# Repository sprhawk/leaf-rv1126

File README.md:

# Leaf RV1126

This work is licensed under a [Creative Commons Attribution-ShareAlike 4.0 International License](http://creativecommons.org/licenses/by-sa/4.0/).

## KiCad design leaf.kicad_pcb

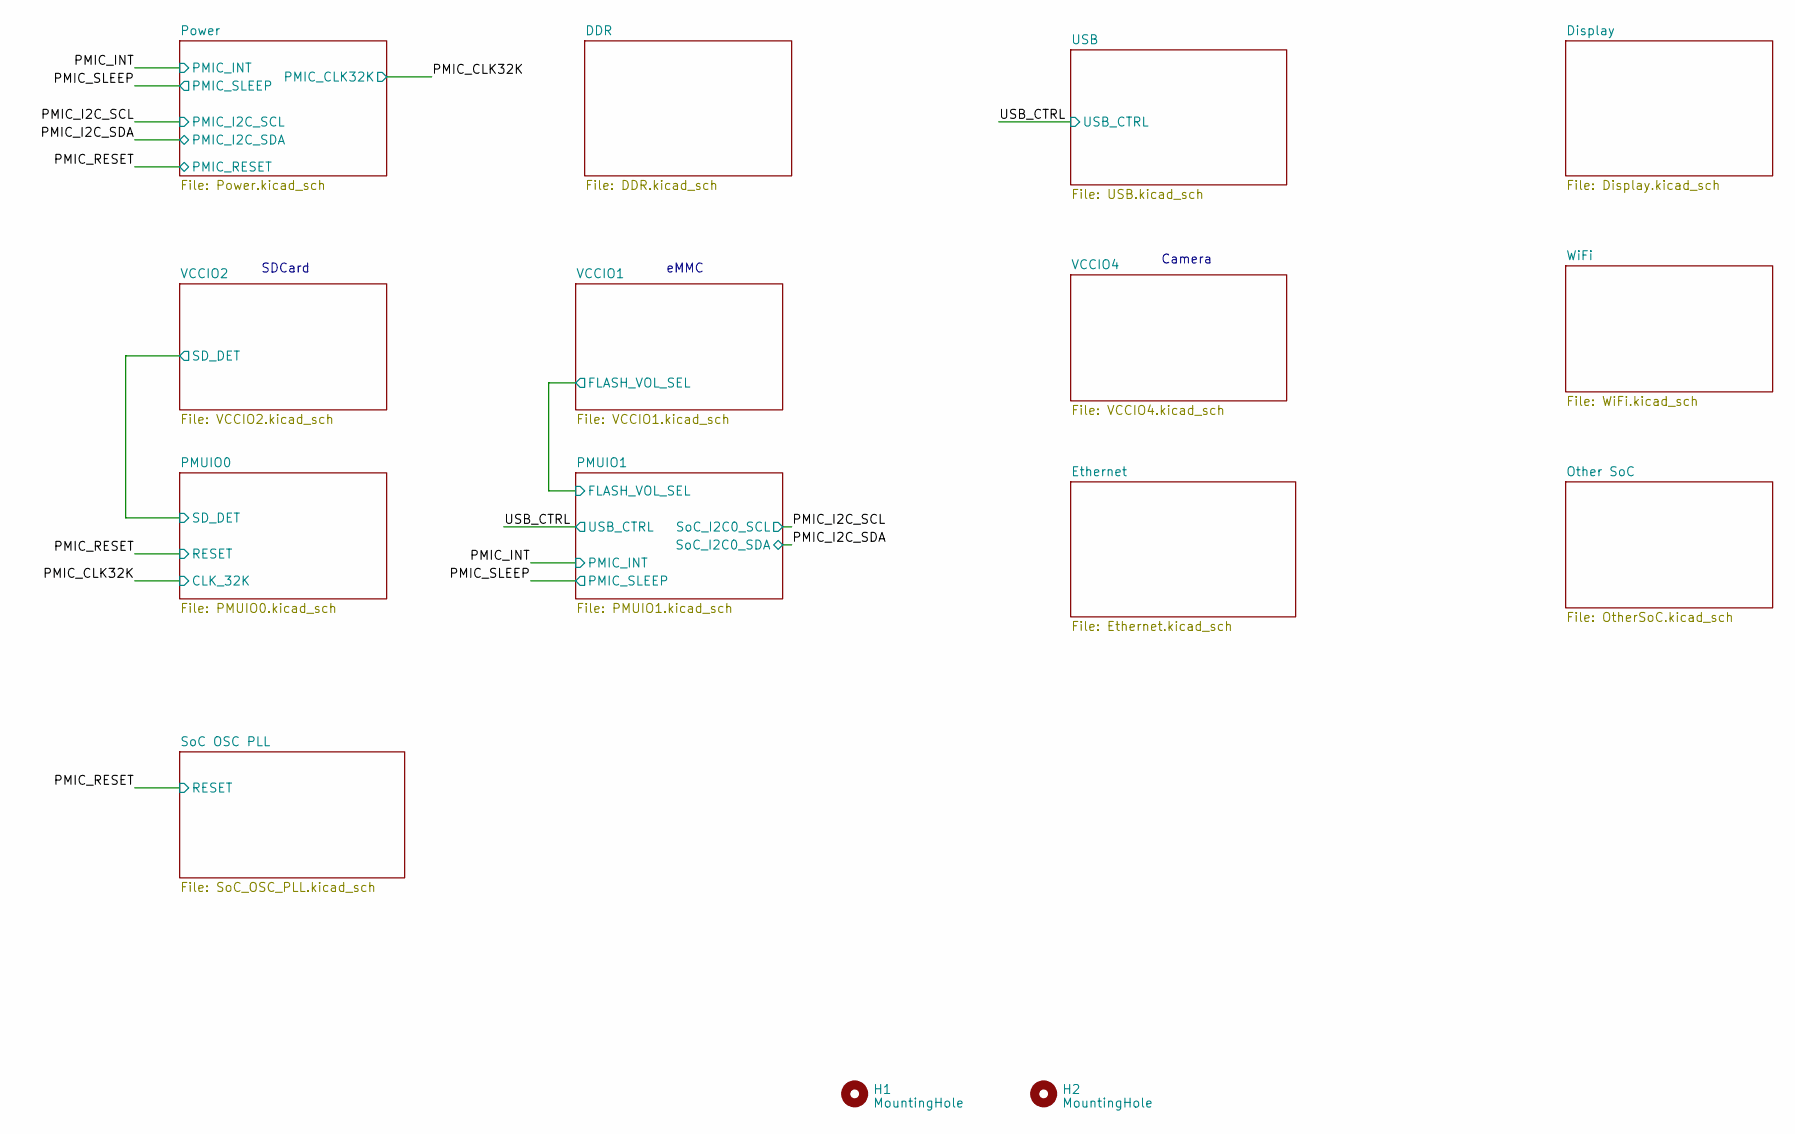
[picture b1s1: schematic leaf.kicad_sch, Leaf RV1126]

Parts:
H1, H2: MountingHole; MountingHole_2.7mm_M2.5

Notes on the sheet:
Camera
SDCard
eMMC

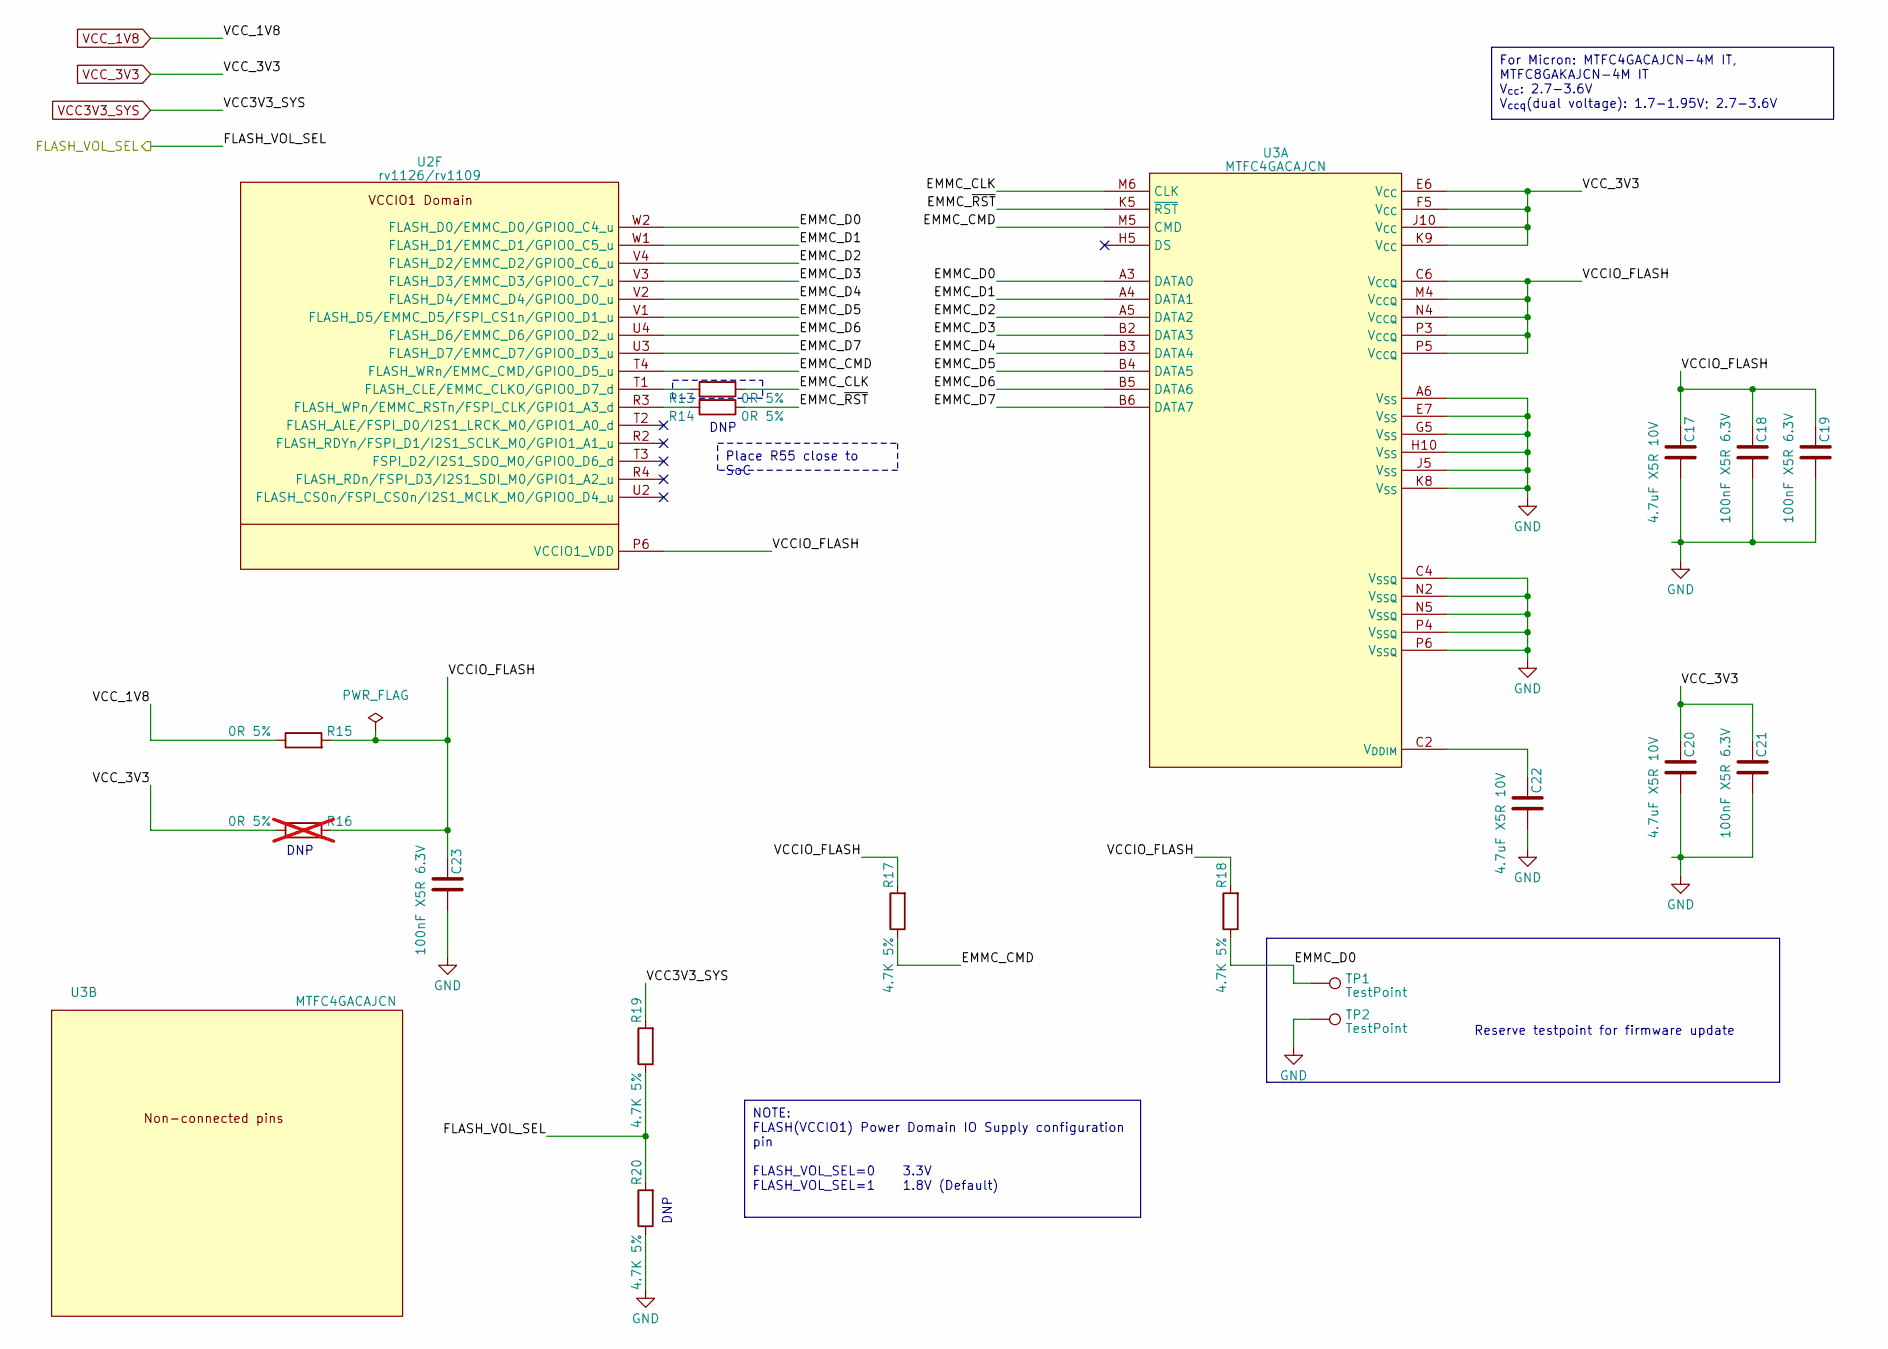
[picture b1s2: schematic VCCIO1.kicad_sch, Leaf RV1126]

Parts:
C17, C20, C22: 4.7uF X5R 10V; C_0402_1005Metric; LCSC C77004
C18, C19, C21, C23: 100nF X5R 6.3V; C_0201_0603Metric; LCSC C76928
R13, R14, R15: 0R 5%; R_0402_1005Metric; LCSC C17168
R16: 0R 5%; R_0402_1005Metric; LCSC C17168; not fitted
R17, R18, R19, R20: 4.7K 5%; R_0402_1005Metric; LCSC C25940
TP1, TP2: TestPoint; TestPoint_Pad_D1.0mm
U2: rv1126/rv1109; Rockchip_RV1126_FCCSP409LD_14.0x14.0mm
U3: MTFC4GACAJCN; Micron_eMMC_FBGA-153_11.5x13.0mm

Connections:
/PMUIO1/FLASH_VOL_SEL: R19.1, R20.2; also elsewhere on the board
/VCCIO1/EMMC_CLK: R13.1, U3.M6 (CLK)
/VCCIO1/EMMC_CMD: R17.1, U2.T4 (FLASH_WRn/EMMC_CMD/GPIO0_D5_u), U3.M5 (CMD)
/VCCIO1/EMMC_D0: R18.1, TP1.1, U2.W2 (FLASH_D0/EMMC_D0/GPIO0_C4_u), U3.A3 (DATA0)
/VCCIO1/EMMC_D1: U2.W1 (FLASH_D1/EMMC_D1/GPIO0_C5_u), U3.A4 (DATA1)
/VCCIO1/EMMC_D2: U2.V4 (FLASH_D2/EMMC_D2/GPIO0_C6_u), U3.A5 (DATA2)
/VCCIO1/EMMC_D3: U2.V3 (FLASH_D3/EMMC_D3/GPIO0_C7_u), U3.B2 (DATA3)
/VCCIO1/EMMC_D4: U2.V2 (FLASH_D4/EMMC_D4/GPIO0_D0_u), U3.B3 (DATA4)
/VCCIO1/EMMC_D5: U2.V1 (FLASH_D5/EMMC_D5/FSPI_CS1n/GPIO0_D1_u), U3.B4 (DATA5)
/VCCIO1/EMMC_D6: U2.U4 (FLASH_D6/EMMC_D6/GPIO0_D2_u), U3.B5 (DATA6)
/VCCIO1/EMMC_D7: U2.U3 (FLASH_D7/EMMC_D7/GPIO0_D3_u), U3.B6 (DATA7)
/VCCIO1/EMMC_~RST: R14.1, U3.K5 (~RST)
/VCCIO1/VCCIO_FLASH: C17.1, C18.1, C19.1, C23.1, R15.2, R16.2, R17.2, R18.2, U2.P6 (VCCIO1_VDD), U3.C6 (V_{CCQ}), U3.M4 (V_{CCQ}), U3.N4 (V_{CCQ}), U3.P3 (V_{CCQ}), U3.P5 (V_{CCQ})
GND: C17.2, C18.2, C19.2, C20.2, C21.2, C22.2, C23.2, R20.1, TP2.1, U3.A6 (V_{SS}), U3.C4 (V_{SSQ}), U3.E7 (V_{SS}), U3.G5 (V_{SS}), U3.H10 (V_{SS}), U3.J5 (V_{SS}), U3.K8 (V_{SS}), U3.N2 (V_{SSQ}), U3.N5 (V_{SSQ}), U3.P4 (V_{SSQ}), U3.P6 (V_{SSQ}); also elsewhere on the board
unnamed: R13.2, U2.T1 (FLASH_CLE/EMMC_CLKO/GPIO0_D7_d)
unnamed: R14.2, U2.R3 (FLASH_WPn/EMMC_RSTn/FSPI_CLK/GPIO1_A3_d)
unnamed: C22.1, U3.C2 (V_{DDIM})
VCC3V3_SYS: R19.2; also elsewhere on the board
VCC_1V8: R15.1; also elsewhere on the board
VCC_3V3: C20.1, C21.1, R16.1, U3.E6 (V_{CC}), U3.F5 (V_{CC}), U3.J10 (V_{CC}), U3.K9 (V_{CC}); also elsewhere on the board

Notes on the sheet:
NOTE: FLASH(VCCIO1) Power Domain IO Supply configuration pin FLASH_VOL_SEL=0 3.3V FLASH_VOL_SEL=1 1.8V (Default)
Place R55 close to SoC
For Micron: MTFC4GACAJCN-4M IT, MTFC8GAKAJCN-4M IT V_{cc}: 2.7-3.6V V_{ccq}(dual voltage): 1.7-1.95V; 2.7-3.6V
DNP
Reserve testpoint for firmware update

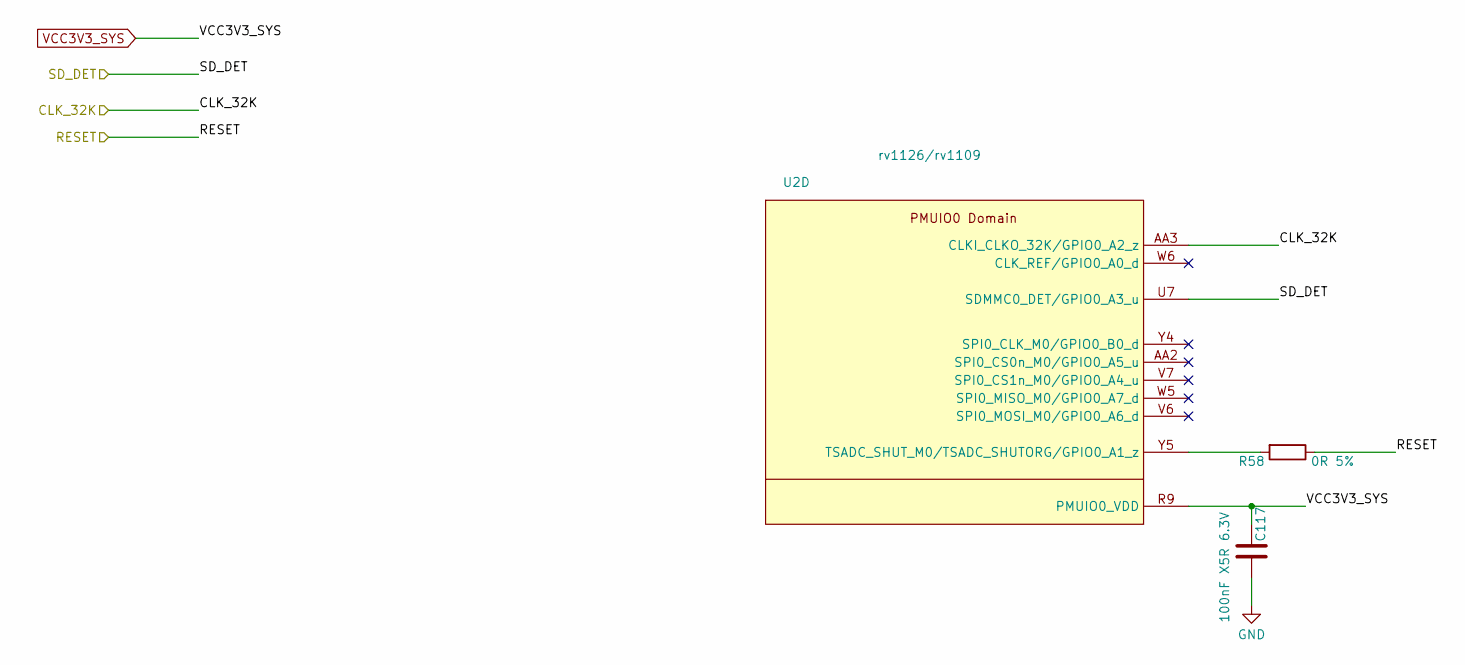
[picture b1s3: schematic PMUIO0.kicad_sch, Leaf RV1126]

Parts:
C117: 100nF X5R 6.3V; C_0201_0603Metric; LCSC C76928
R58: 0R 5%; R_0402_1005Metric; LCSC C17168
U2: rv1126/rv1109; Rockchip_RV1126_FCCSP409LD_14.0x14.0mm

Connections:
/PMIC_CLK32K: U2.AA3 (CLKI_CLKO_32K/GPIO0_A2_z); also elsewhere on the board
/PMIC_RESET: R58.1; also elsewhere on the board
/PMUIO0/SD_DET: U2.U7 (SDMMC0_DET/GPIO0_A3_u); also elsewhere on the board
GND: C117.2; also elsewhere on the board
unnamed: R58.2, U2.Y5 (TSADC_SHUT_M0/TSADC_SHUTORG/GPIO0_A1_z)
VCC3V3_SYS: C117.1, U2.R9 (PMUIO0_VDD); also elsewhere on the board

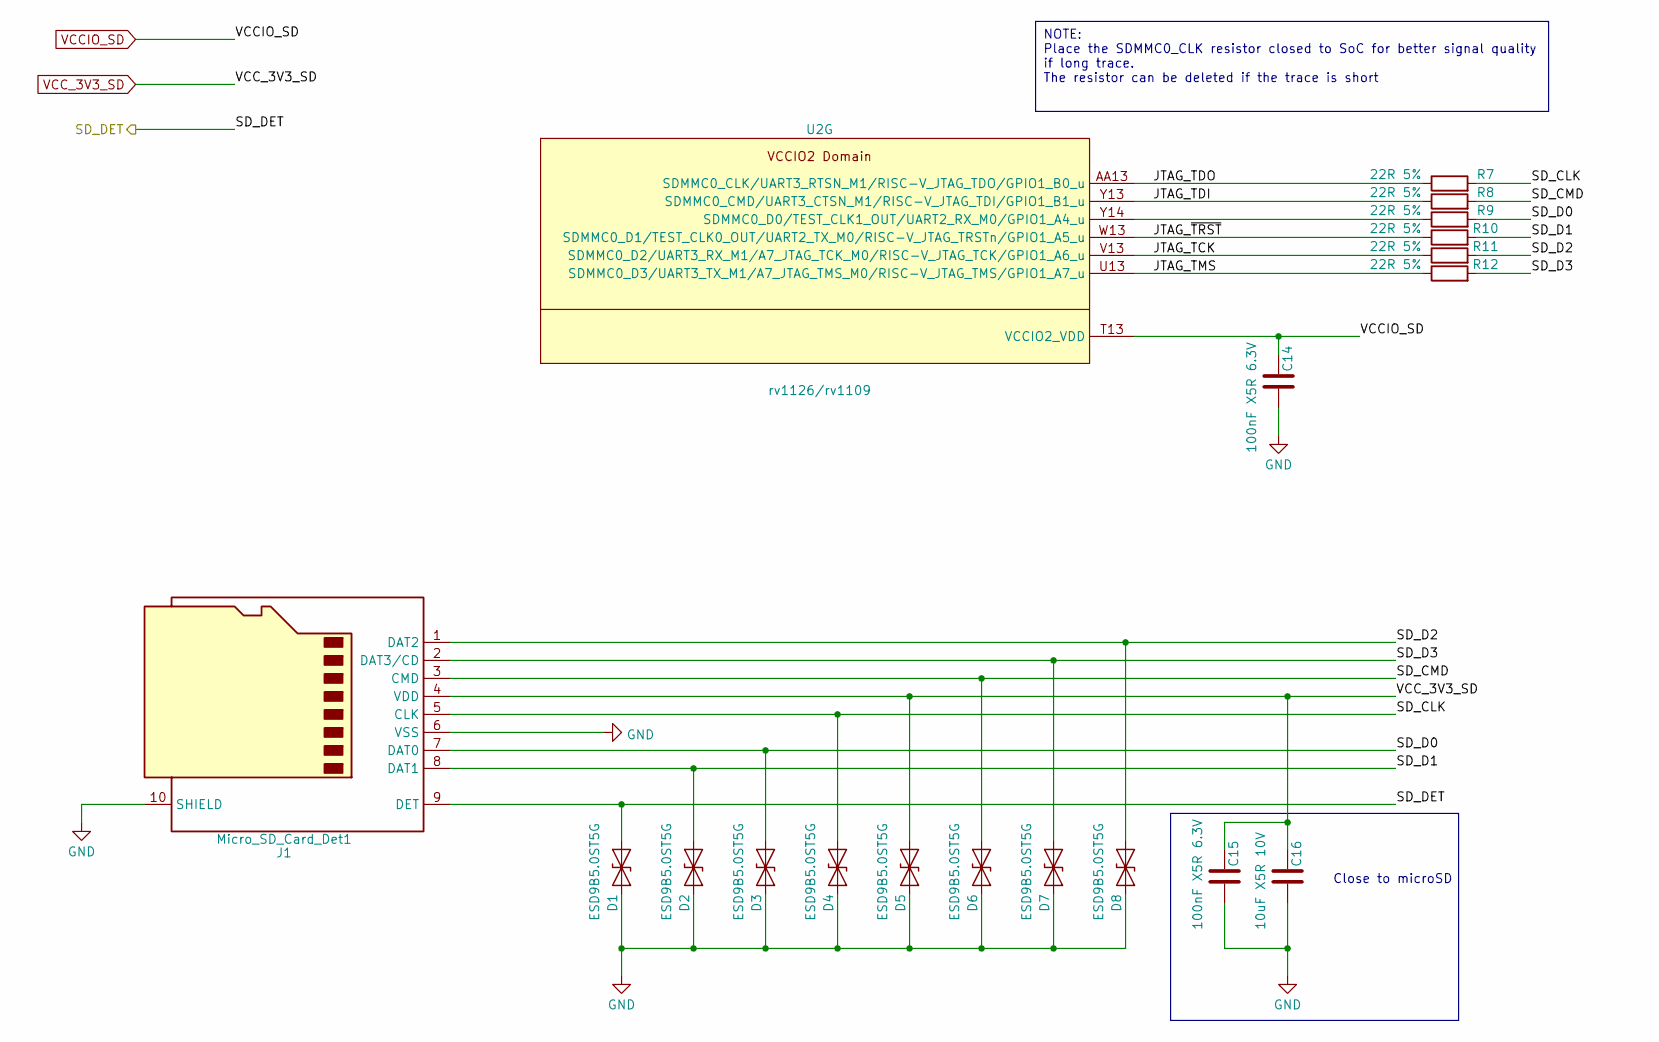
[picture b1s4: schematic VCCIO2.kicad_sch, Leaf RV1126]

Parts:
C14, C15: 100nF X5R 6.3V; C_0201_0603Metric; LCSC C76928
C16: 10uF X5R 10V; C_0402_1005Metric; LCSC C77000
D1, D2, D3, D4, D5, D6, D7, D8: ESD9B5.0ST5G; D_SOD-923
J1: Micro_SD_Card_Det1; microSD; LCSC C2982548
R7, R8, R9, R10, R11, R12: 22R 5%; R_0402_1005Metric; LCSC C59651
U2: rv1126/rv1109; Rockchip_RV1126_FCCSP409LD_14.0x14.0mm

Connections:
/PMUIO0/SD_DET: D1.1 (A1), J1.9 (DET); also elsewhere on the board
/VCCIO2/JTAG_TCK: R11.1, U2.V13 (SDMMC0_D2/UART3_RX_M1/A7_JTAG_TCK_M0/RI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)
/VCCIO2/JTAG_TDI: R8.1, U2.Y13 (SDMMC0_CMD/UART3_CTSN_M1/RISC-V_JTAG_TD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)
/VCCIO2/JTAG_TDO: R7.1, U2.AA13 (SDMMC0_CLK/UART3_RTSN_M1/RISC-V_JTAG_TD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)
/VCCIO2/JTAG_TMS: R12.1, U2.U13 (SDMMC0_D3/UART3_TX_M1/A7_JTAG_TMS_M0/RI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)
/VCCIO2/JTAG_~TRST: R10.1, U2.W13 (SDMMC0_D1/TEST_CLK0_OUT/UART2_TX_M0/RIS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)
/VCCIO2/SD_CLK: D4.1 (A1), J1.5 (CLK), R7.2
/VCCIO2/SD_CMD: D6.1 (A1), J1.3 (CMD), R8.2
/VCCIO2/SD_D0: D3.1 (A1), J1.7 (DAT0), R9.2
/VCCIO2/SD_D1: D2.1 (A1), J1.8 (DAT1), R10.2
/VCCIO2/SD_D2: D8.1 (A1), J1.1 (DAT2), R11.2
/VCCIO2/SD_D3: D7.1 (A1), J1.2 (DAT3/CD), R12.2
GND: C14.2, C15.2, C16.2, D1.2 (A2), D2.2 (A2), D3.2 (A2), D4.2 (A2), D5.2 (A2), D6.2 (A2), D7.2 (A2), D8.2 (A2), J1.6 (VSS), J1.10 (SHIELD); also elsewhere on the board
unnamed: R9.1, U2.Y14 (SDMMC0_D0/TEST_CLK1_OUT/UART2_RX_M0/GPI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)
VCCIO_SD: C14.1, U2.T13 (VCCIO2_VDD); also elsewhere on the board
VCC_3V3_SD: C15.1, C16.1, D5.1 (A1), J1.4 (VDD); also elsewhere on the board

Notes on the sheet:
NOTE: Place the SDMMC0_CLK resistor closed to SoC for better signal quality if long trace. The resistor can be deleted if the trace is short
Close to microSD

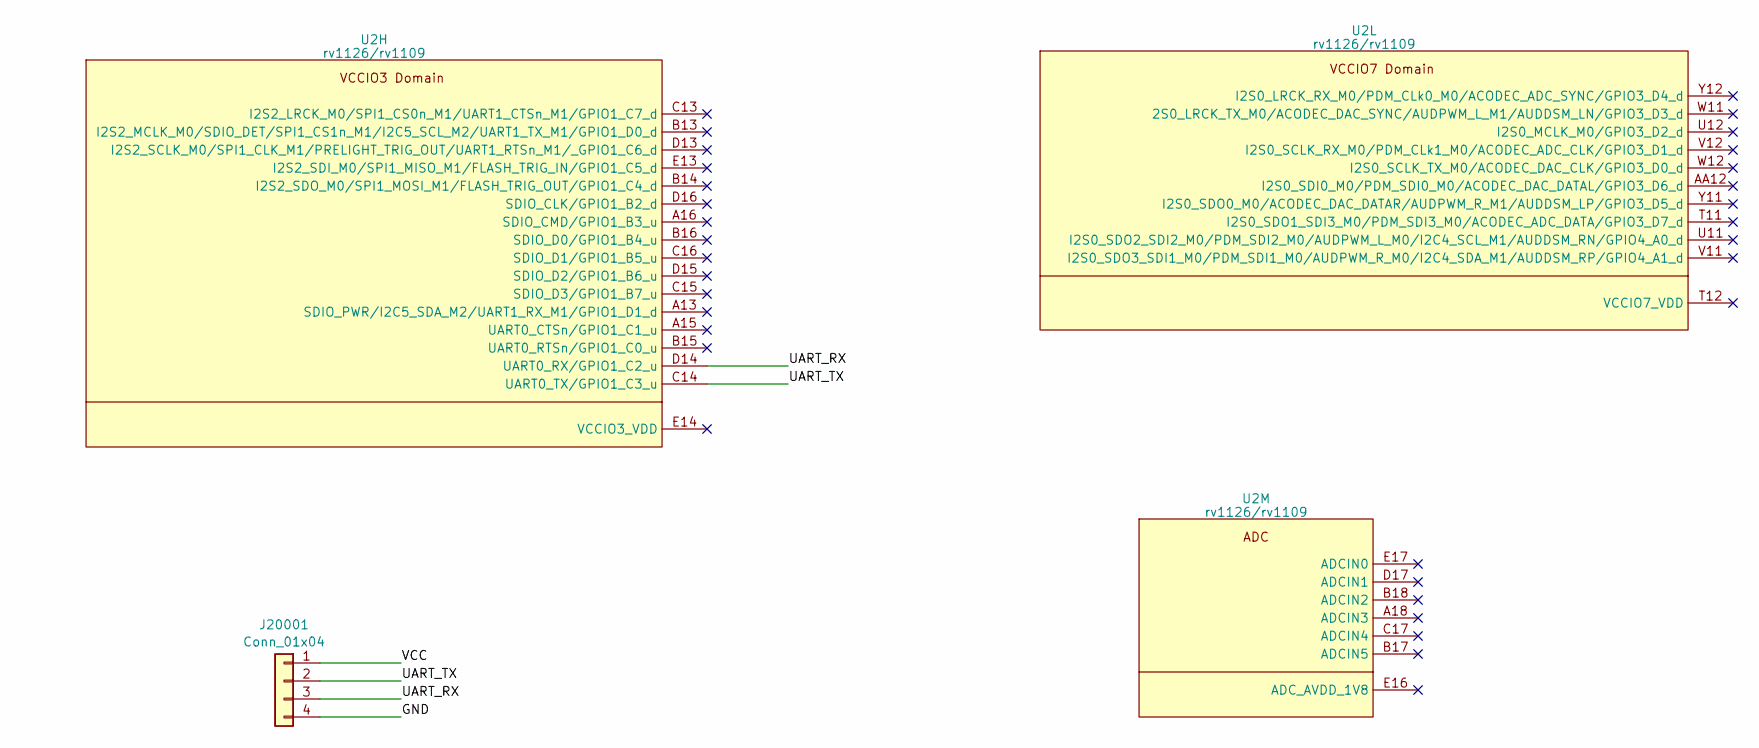
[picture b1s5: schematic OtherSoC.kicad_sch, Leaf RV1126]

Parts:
J20001: Conn_01x04
U2: rv1126/rv1109; Rockchip_RV1126_FCCSP409LD_14.0x14.0mm

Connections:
/Other SoC/UART_RX: J20001.3, U2.D14 (UART0_RX/GPIO1_C2_u)
/Other SoC/UART_TX: J20001.2, U2.C14 (UART0_TX/GPIO1_C3_u)

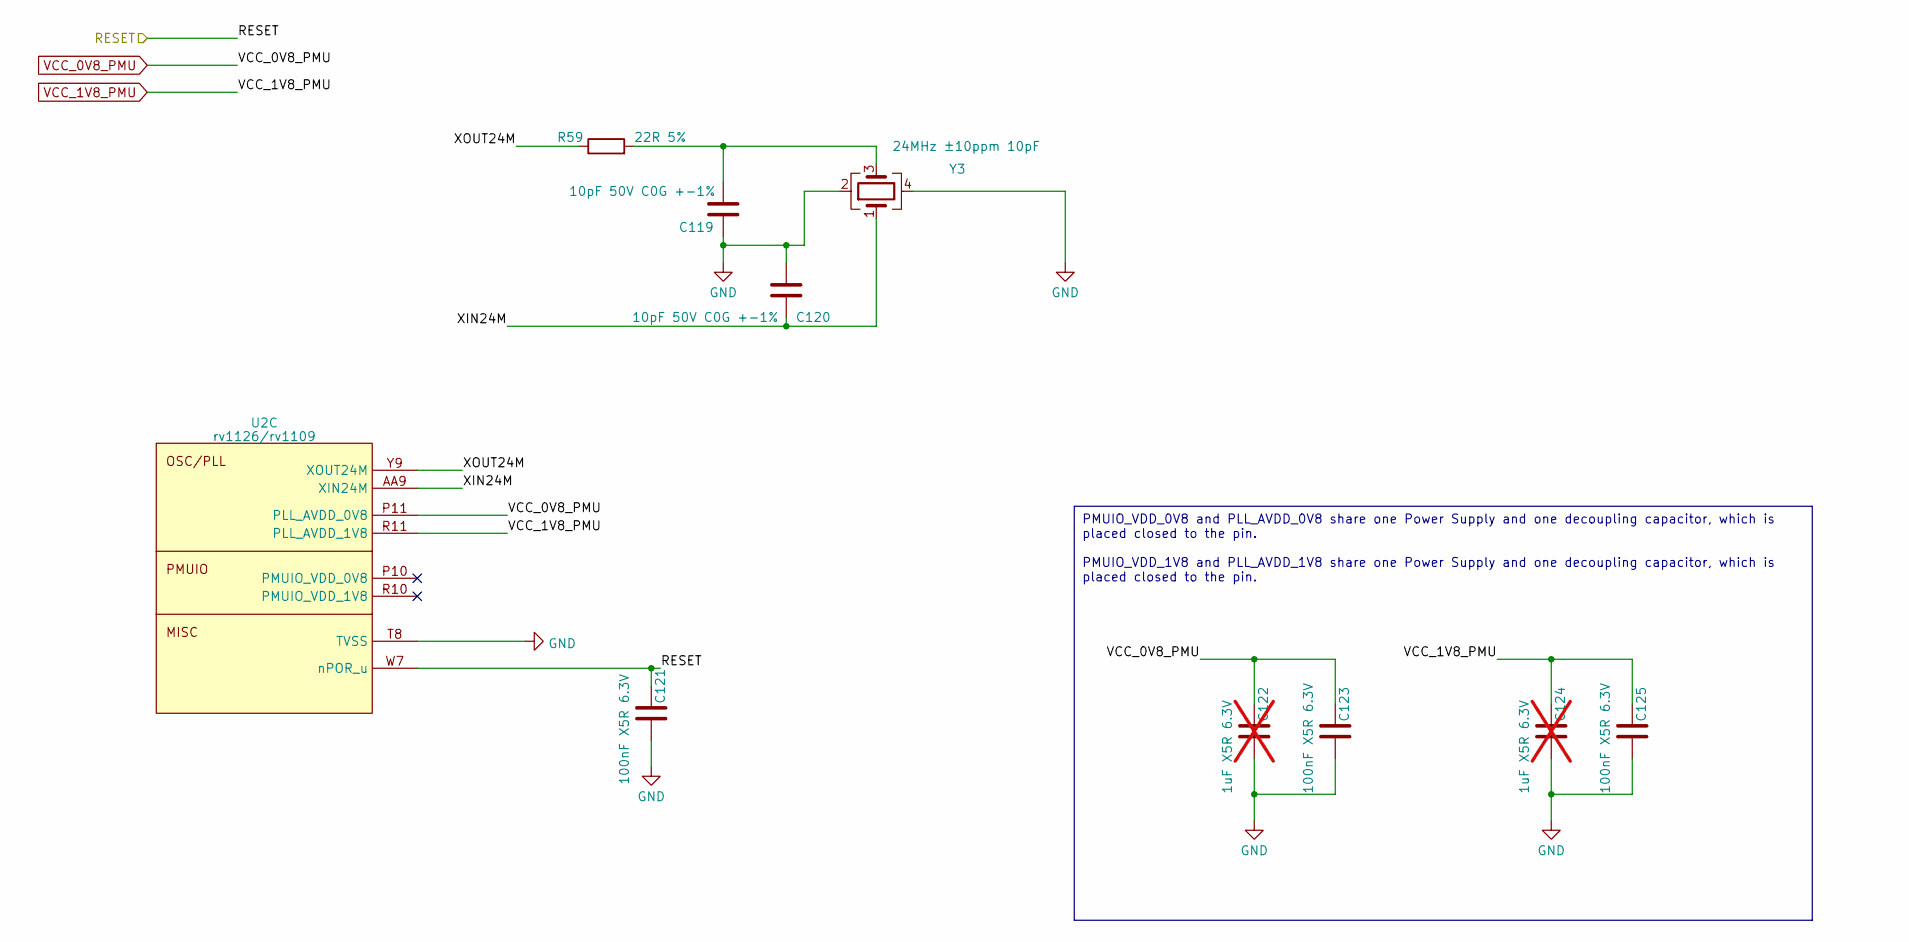
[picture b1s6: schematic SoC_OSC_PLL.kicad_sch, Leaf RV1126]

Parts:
C119, C120: 10pF 50V C0G +-1%; C_0402_1005Metric; LCSC C161145
C121, C123, C125: 100nF X5R 6.3V; C_0201_0603Metric; LCSC C76928
C122, C124: 1uF X5R 6.3V; C_0402_1005Metric; LCSC C15684; not fitted
R59: 22R 5%; R_0402_1005Metric; LCSC C59651
U2: rv1126/rv1109; Rockchip_RV1126_FCCSP409LD_14.0x14.0mm
Y3: 24MHz ±10ppm 10pF; Crystal_SMD_2520-4Pin_2.5x2.0mm; LCSC C255953

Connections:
/PMIC_RESET: C121.1, U2.W7 (nPOR_u); also elsewhere on the board
/SoC OSC PLL/XIN24M: C120.2, U2.AA9 (XIN24M), Y3.1
/SoC OSC PLL/XOUT24M: R59.1, U2.Y9 (XOUT24M)
GND: C119.1, C120.1, C121.2, C122.2, C123.2, C124.2, C125.2, U2.T8 (TVSS), Y3.2, Y3.4; also elsewhere on the board
unnamed: C119.2, R59.2, Y3.3
VCC_0V8_PMU: C122.1, C123.1, U2.P11 (PLL_AVDD_0V8); also elsewhere on the board
VCC_1V8_PMU: C124.1, C125.1, U2.R11 (PLL_AVDD_1V8); also elsewhere on the board

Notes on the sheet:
PMUIO_VDD_0V8 and PLL_AVDD_0V8 share one Power Supply and one decoupling capacitor, which is placed closed to the pin. PMUIO_VDD_1V8 and PLL_AVDD_1V8 share one Power Supply and one decoupling capacitor, which is placed closed to the pin.

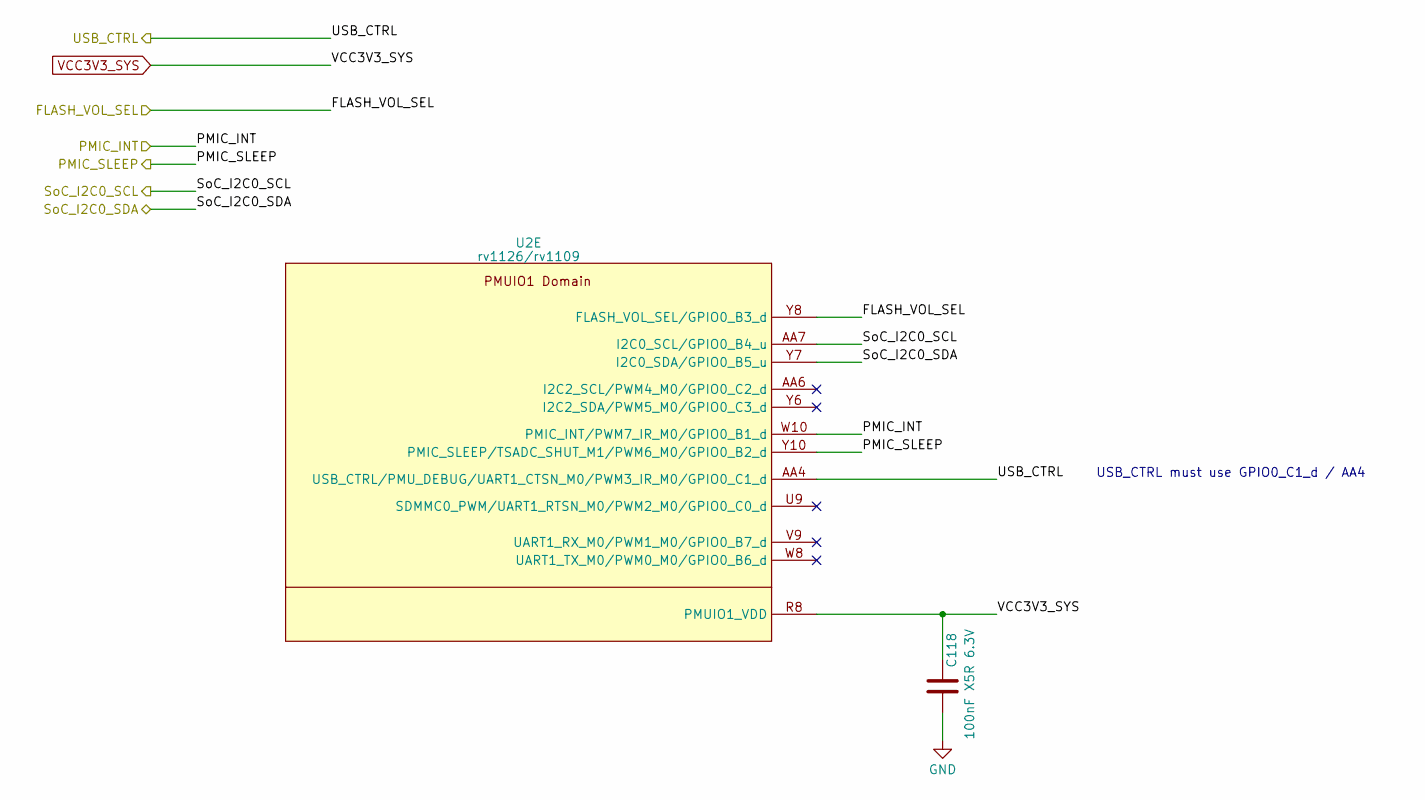
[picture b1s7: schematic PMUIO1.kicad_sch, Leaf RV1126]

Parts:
C118: 100nF X5R 6.3V; C_0201_0603Metric; LCSC C76928
U2: rv1126/rv1109; Rockchip_RV1126_FCCSP409LD_14.0x14.0mm

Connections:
/PMIC_I2C_SCL: U2.AA7 (I2C0_SCL/GPIO0_B4_u); also elsewhere on the board
/PMIC_I2C_SDA: U2.Y7 (I2C0_SDA/GPIO0_B5_u); also elsewhere on the board
/PMIC_INT: U2.W10 (PMIC_INT/PWM7_IR_M0/GPIO0_B1_d); also elsewhere on the board
/PMIC_SLEEP: U2.Y10 (PMIC_SLEEP/TSADC_SHUT_M1/PWM6_M0/GPIO0_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); also elsewhere on the board
/PMUIO1/FLASH_VOL_SEL: U2.Y8 (FLASH_VOL_SEL/GPIO0_B3_d); also elsewhere on the board
/USB_CTRL: U2.AA4 (USB_CTRL/PMU_DEBUG/UART1_CTSN_M0/PWM3_I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); also elsewhere on the board
GND: C118.2; also elsewhere on the board
VCC3V3_SYS: C118.1, U2.R8 (PMUIO1_VDD); also elsewhere on the board

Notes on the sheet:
USB_CTRL must use GPIO0_C1_d / AA4

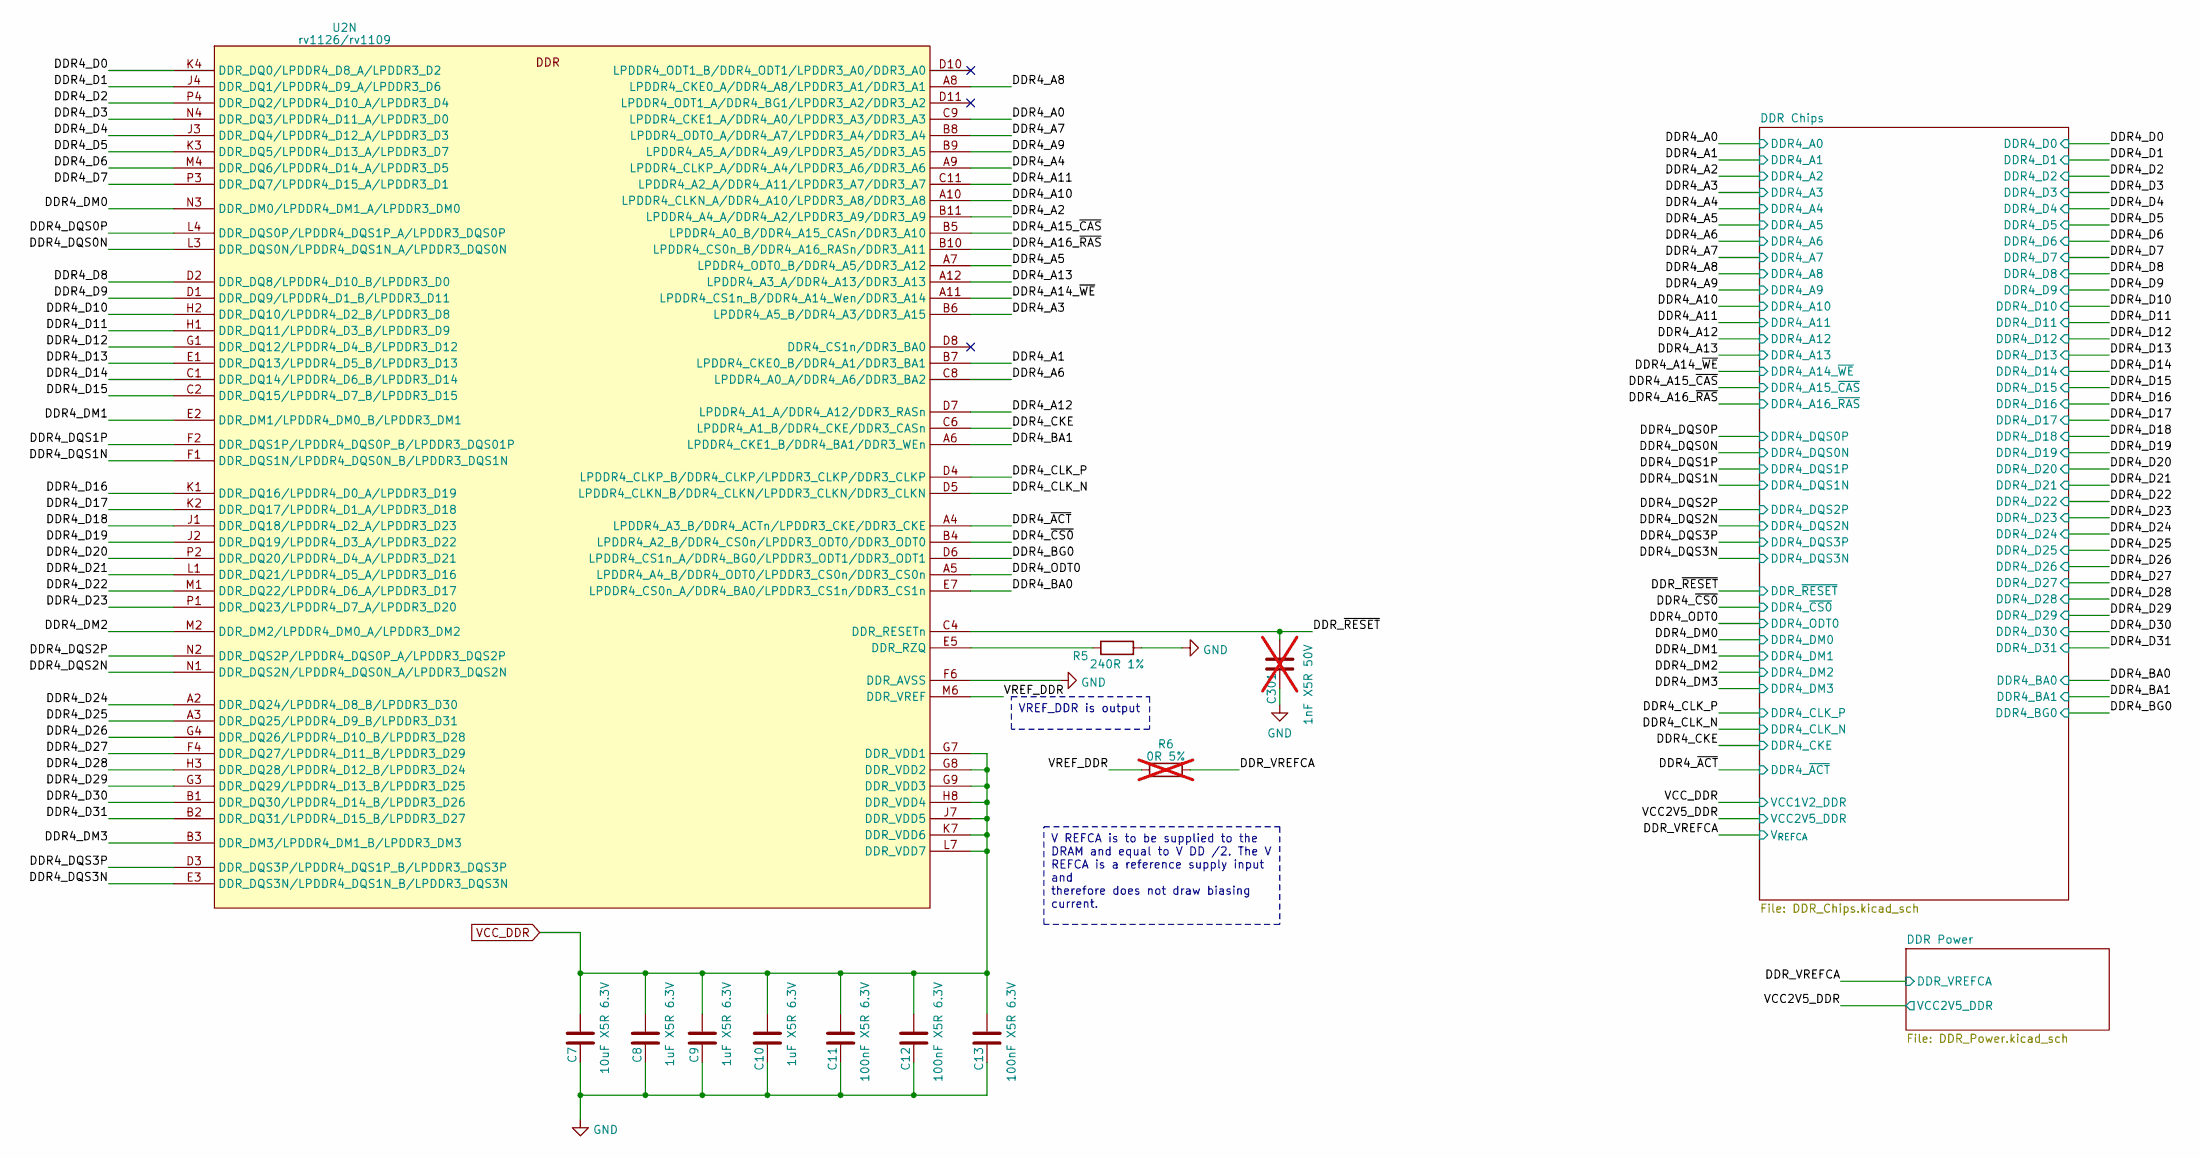
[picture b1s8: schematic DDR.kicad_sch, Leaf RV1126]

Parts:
C7: 10uF X5R 6.3V; C_0603_1608Metric; LCSC C77041
C8, C9, C10: 1uF X5R 6.3V; C_0402_1005Metric; LCSC C15684
C11, C12, C13: 100nF X5R 6.3V; C_0201_0603Metric; LCSC C76928
C301: 1nF X5R 50V; C_0402_1005Metric; LCSC C77018; not fitted
R5: 240R 1%; R_0201_0603Metric
R6: 0R 5%; R_0402_1005Metric; LCSC C17168; not fitted
U2: rv1126/rv1109; Rockchip_RV1126_FCCSP409LD_14.0x14.0mm

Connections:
/DDR/DDR4_A0: U2.C9 (LPDDR4_CKE1_A/DDR4_A0/LPDDR3_A3/DDR3_A3); also elsewhere on the board
/DDR/DDR4_A1: U2.B7 (LPDDR4_CKE0_B/DDR4_A1/DDR3_BA1); also elsewhere on the board
/DDR/DDR4_A2: U2.B11 (LPDDR4_A4_A/DDR4_A2/LPDDR3_A9/DDR3_A9); also elsewhere on the board
/DDR/DDR4_A3: U2.B6 (LPDDR4_A5_B/DDR4_A3/DDR3_A15); also elsewhere on the board
/DDR/DDR4_A4: U2.A9 (LPDDR4_CLKP_A/DDR4_A4/LPDDR3_A6/DDR3_A6); also elsewhere on the board
/DDR/DDR4_A5: U2.A7 (LPDDR4_ODT0_B/DDR4_A5/DDR3_A12); also elsewhere on the board
/DDR/DDR4_A6: U2.C8 (LPDDR4_A0_A/DDR4_A6/DDR3_BA2); also elsewhere on the board
/DDR/DDR4_A7: U2.B8 (LPDDR4_ODT0_A/DDR4_A7/LPDDR3_A4/DDR3_A4); also elsewhere on the board
/DDR/DDR4_A8: U2.A8 (LPDDR4_CKE0_A/DDR4_A8/LPDDR3_A1/DDR3_A1); also elsewhere on the board
/DDR/DDR4_A9: U2.B9 (LPDDR4_A5_A/DDR4_A9/LPDDR3_A5/DDR3_A5); also elsewhere on the board
/DDR/DDR4_A10: U2.A10 (LPDDR4_CLKN_A/DDR4_A10/LPDDR3_A8/DDR3_A8); also elsewhere on the board
/DDR/DDR4_A11: U2.C11 (LPDDR4_A2_A/DDR4_A11/LPDDR3_A7/DDR3_A7); also elsewhere on the board
/DDR/DDR4_A12: U2.D7 (LPDDR4_A1_A/DDR4_A12/DDR3_RASn); also elsewhere on the board
/DDR/DDR4_A13: U2.A12 (LPDDR4_A3_A/DDR4_A13/DDR3_A13); also elsewhere on the board
/DDR/DDR4_A14_~WE: U2.A11 (LPDDR4_CS1n_B/DDR4_A14_Wen/DDR3_A14); also elsewhere on the board
/DDR/DDR4_A15_~CAS: U2.B5 (LPDDR4_A0_B/DDR4_A15_CASn/DDR3_A10); also elsewhere on the board
/DDR/DDR4_A16_~RAS: U2.B10 (LPDDR4_CS0n_B/DDR4_A16_RASn/DDR3_A11); also elsewhere on the board
/DDR/DDR4_BA0: U2.E7 (LPDDR4_CS0n_A/DDR4_BA0/LPDDR3_CS1n/DDR3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); also elsewhere on the board
/DDR/DDR4_BA1: U2.A6 (LPDDR4_CKE1_B/DDR4_BA1/DDR3_WEn); also elsewhere on the board
/DDR/DDR4_BG0: U2.D6 (LPDDR4_CS1n_A/DDR4_BG0/LPDDR3_ODT1/DDR3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); also elsewhere on the board
/DDR/DDR4_CKE: U2.C6 (LPDDR4_A1_B/DDR4_CKE/DDR3_CASn); also elsewhere on the board
/DDR/DDR4_CLK_N: U2.D5 (LPDDR4_CLKN_B/DDR4_CLKN/LPDDR3_CLKN/DDR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); also elsewhere on the board
/DDR/DDR4_CLK_P: U2.D4 (LPDDR4_CLKP_B/DDR4_CLKP/LPDDR3_CLKP/DDR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); also elsewhere on the board
/DDR/DDR4_D0: U2.K4 (DDR_DQ0/LPDDR4_D8_A/LPDDR3_D2); also elsewhere on the board
/DDR/DDR4_D1: U2.J4 (DDR_DQ1/LPDDR4_D9_A/LPDDR3_D6); also elsewhere on the board
/DDR/DDR4_D2: U2.P4 (DDR_DQ2/LPDDR4_D10_A/LPDDR3_D4); also elsewhere on the board
/DDR/DDR4_D3: U2.N4 (DDR_DQ3/LPDDR4_D11_A/LPDDR3_D0); also elsewhere on the board
/DDR/DDR4_D4: U2.J3 (DDR_DQ4/LPDDR4_D12_A/LPDDR3_D3); also elsewhere on the board
/DDR/DDR4_D5: U2.K3 (DDR_DQ5/LPDDR4_D13_A/LPDDR3_D7); also elsewhere on the board
/DDR/DDR4_D6: U2.M4 (DDR_DQ6/LPDDR4_D14_A/LPDDR3_D5); also elsewhere on the board
/DDR/DDR4_D7: U2.P3 (DDR_DQ7/LPDDR4_D15_A/LPDDR3_D1); also elsewhere on the board
/DDR/DDR4_D8: U2.D2 (DDR_DQ8/LPDDR4_D10_B/LPDDR3_D0); also elsewhere on the board
/DDR/DDR4_D9: U2.D1 (DDR_DQ9/LPDDR4_D1_B/LPDDR3_D11); also elsewhere on the board
/DDR/DDR4_D10: U2.H2 (DDR_DQ10/LPDDR4_D2_B/LPDDR3_D8); also elsewhere on the board
/DDR/DDR4_D11: U2.H1 (DDR_DQ11/LPDDR4_D3_B/LPDDR3_D9); also elsewhere on the board
/DDR/DDR4_D12: U2.G1 (DDR_DQ12/LPDDR4_D4_B/LPDDR3_D12); also elsewhere on the board
/DDR/DDR4_D13: U2.E1 (DDR_DQ13/LPDDR4_D5_B/LPDDR3_D13); also elsewhere on the board
/DDR/DDR4_D14: U2.C1 (DDR_DQ14/LPDDR4_D6_B/LPDDR3_D14); also elsewhere on the board
/DDR/DDR4_D15: U2.C2 (DDR_DQ15/LPDDR4_D7_B/LPDDR3_D15); also elsewhere on the board
/DDR/DDR4_D16: U2.K1 (DDR_DQ16/LPDDR4_D0_A/LPDDR3_D19); also elsewhere on the board
/DDR/DDR4_D17: U2.K2 (DDR_DQ17/LPDDR4_D1_A/LPDDR3_D18); also elsewhere on the board
/DDR/DDR4_D18: U2.J1 (DDR_DQ18/LPDDR4_D2_A/LPDDR3_D23); also elsewhere on the board
/DDR/DDR4_D19: U2.J2 (DDR_DQ19/LPDDR4_D3_A/LPDDR3_D22); also elsewhere on the board
/DDR/DDR4_D20: U2.P2 (DDR_DQ20/LPDDR4_D4_A/LPDDR3_D21); also elsewhere on the board
/DDR/DDR4_D21: U2.L1 (DDR_DQ21/LPDDR4_D5_A/LPDDR3_D16); also elsewhere on the board
/DDR/DDR4_D22: U2.M1 (DDR_DQ22/LPDDR4_D6_A/LPDDR3_D17); also elsewhere on the board
/DDR/DDR4_D23: U2.P1 (DDR_DQ23/LPDDR4_D7_A/LPDDR3_D20); also elsewhere on the board
/DDR/DDR4_D24: U2.A2 (DDR_DQ24/LPDDR4_D8_B/LPDDR3_D30); also elsewhere on the board
/DDR/DDR4_D25: U2.A3 (DDR_DQ25/LPDDR4_D9_B/LPDDR3_D31); also elsewhere on the board
/DDR/DDR4_D26: U2.G4 (DDR_DQ26/LPDDR4_D10_B/LPDDR3_D28); also elsewhere on the board
/DDR/DDR4_D27: U2.F4 (DDR_DQ27/LPDDR4_D11_B/LPDDR3_D29); also elsewhere on the board
/DDR/DDR4_D28: U2.H3 (DDR_DQ28/LPDDR4_D12_B/LPDDR3_D24); also elsewhere on the board
/DDR/DDR4_D29: U2.G3 (DDR_DQ29/LPDDR4_D13_B/LPDDR3_D25); also elsewhere on the board
/DDR/DDR4_D30: U2.B1 (DDR_DQ30/LPDDR4_D14_B/LPDDR3_D26); also elsewhere on the board
/DDR/DDR4_D31: U2.B2 (DDR_DQ31/LPDDR4_D15_B/LPDDR3_D27); also elsewhere on the board
/DDR/DDR4_DM0: U2.N3 (DDR_DM0/LPDDR4_DM1_A/LPDDR3_DM0); also elsewhere on the board
/DDR/DDR4_DM1: U2.E2 (DDR_DM1/LPDDR4_DM0_B/LPDDR3_DM1); also elsewhere on the board
/DDR/DDR4_DM2: U2.M2 (DDR_DM2/LPDDR4_DM0_A/LPDDR3_DM2); also elsewhere on the board
/DDR/DDR4_DM3: U2.B3 (DDR_DM3/LPDDR4_DM1_B/LPDDR3_DM3); also elsewhere on the board
/DDR/DDR4_DQS0N: U2.L3 (DDR_DQS0N/LPDDR4_DQS1N_A/LPDDR3_DQS0N); also elsewhere on the board
/DDR/DDR4_DQS0P: U2.L4 (DDR_DQS0P/LPDDR4_DQS1P_A/LPDDR3_DQS0P); also elsewhere on the board
/DDR/DDR4_DQS1N: U2.F1 (DDR_DQS1N/LPDDR4_DQS0N_B/LPDDR3_DQS1N); also elsewhere on the board
/DDR/DDR4_DQS1P: U2.F2 (DDR_DQS1P/LPDDR4_DQS0P_B/LPDDR3_DQS01P); also elsewhere on the board
/DDR/DDR4_DQS2N: U2.N1 (DDR_DQS2N/LPDDR4_DQS0N_A/LPDDR3_DQS2N); also elsewhere on the board
/DDR/DDR4_DQS2P: U2.N2 (DDR_DQS2P/LPDDR4_DQS0P_A/LPDDR3_DQS2P); also elsewhere on the board
/DDR/DDR4_DQS3N: U2.E3 (DDR_DQS3N/LPDDR4_DQS1N_B/LPDDR3_DQS3N); also elsewhere on the board
/DDR/DDR4_DQS3P: U2.D3 (DDR_DQS3P/LPDDR4_DQS1P_B/LPDDR3_DQS3P); also elsewhere on the board
/DDR/DDR4_ODT0: U2.A5 (LPDDR4_A4_B/DDR4_ODT0/LPDDR3_CS0n/DDR3_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); also elsewhere on the board
/DDR/DDR4_~ACT: U2.A4 (LPDDR4_A3_B/DDR4_ACTn/LPDDR3_CKE/DDR3_C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); also elsewhere on the board
/DDR/DDR4_~CS0: U2.B4 (LPDDR4_A2_B/DDR4_CS0n/LPDDR3_ODT0/DDR3_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); also elsewhere on the board
/DDR/DDR_VREFCA: R6.2; also elsewhere on the board
/DDR/DDR_~RESET: C301.2, U2.C4 (DDR_RESETn); also elsewhere on the board
/DDR/VREF_DDR: R6.1, U2.M6 (DDR_VREF)
GND: C7.1, C8.1, C9.1, C10.1, C11.1, C12.1, C13.1, C301.1, R5.2, U2.F6 (DDR_AVSS); also elsewhere on the board
unnamed: R5.1, U2.E5 (DDR_RZQ)
VCC_DDR: C7.2, C8.2, C9.2, C10.2, C11.2, C12.2, C13.2, U2.G7 (DDR_VDD1), U2.G8 (DDR_VDD2), U2.G9 (DDR_VDD3), U2.H8 (DDR_VDD4), U2.J7 (DDR_VDD5), U2.K7 (DDR_VDD6), U2.L7 (DDR_VDD7); also elsewhere on the board

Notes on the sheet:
VREF_DDR is output
V REFCA is to be supplied to the DRAM and equal to V DD /2. The V REFCA is a reference supply input and therefore does not draw biasing current.

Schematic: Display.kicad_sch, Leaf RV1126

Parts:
U2: rv1126/rv1109; Rockchip_RV1126_FCCSP409LD_14.0x14.0mm

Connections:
/Display/MIPI_DSI_AVDD_0V8: U2.E18 (MIPI_DSI_TX0_AVDD_0V8)
/Display/MIPI_DSI_AVDD_1V8: U2.G15 (MIPI_DSI_TX0_AVDD_1V8)
/Display/MIPI_DSI_TX0_CLKN: U2.C18 (MIPI_DSI_TX0_CLKN)
/Display/MIPI_DSI_TX0_CLKP: U2.C19 (MIPI_DSI_TX0_CLKP)
/Display/MIPI_DSI_TX0_D0N: U2.B19 (MIPI_DSI_TX0_D0N)
/Display/MIPI_DSI_TX0_D0P: U2.A19 (MIPI_DSI_TX0_D0P)
/Display/MIPI_DSI_TX0_D1N: U2.B20 (MIPI_DSI_TX0_D1N)
/Display/MIPI_DSI_TX0_D1P: U2.A20 (MIPI_DSI_TX0_D1P)
/Display/MIPI_DSI_TX0_D2N: U2.C20 (MIPI_DSI_TX0_D2N)
/Display/MIPI_DSI_TX0_D2P: U2.B21 (MIPI_DSI_TX0_D2P)
/Display/MIPI_DSI_TX0_D3N: U2.D19 (MIPI_DSI_TX0_D3N)
/Display/MIPI_DSI_TX0_D3P: U2.D20 (MIPI_DSI_TX0_D3P)

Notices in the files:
DDR.kicad_sch:
License: CC BY-SA
README.md:
CC BY-SA 4.0
